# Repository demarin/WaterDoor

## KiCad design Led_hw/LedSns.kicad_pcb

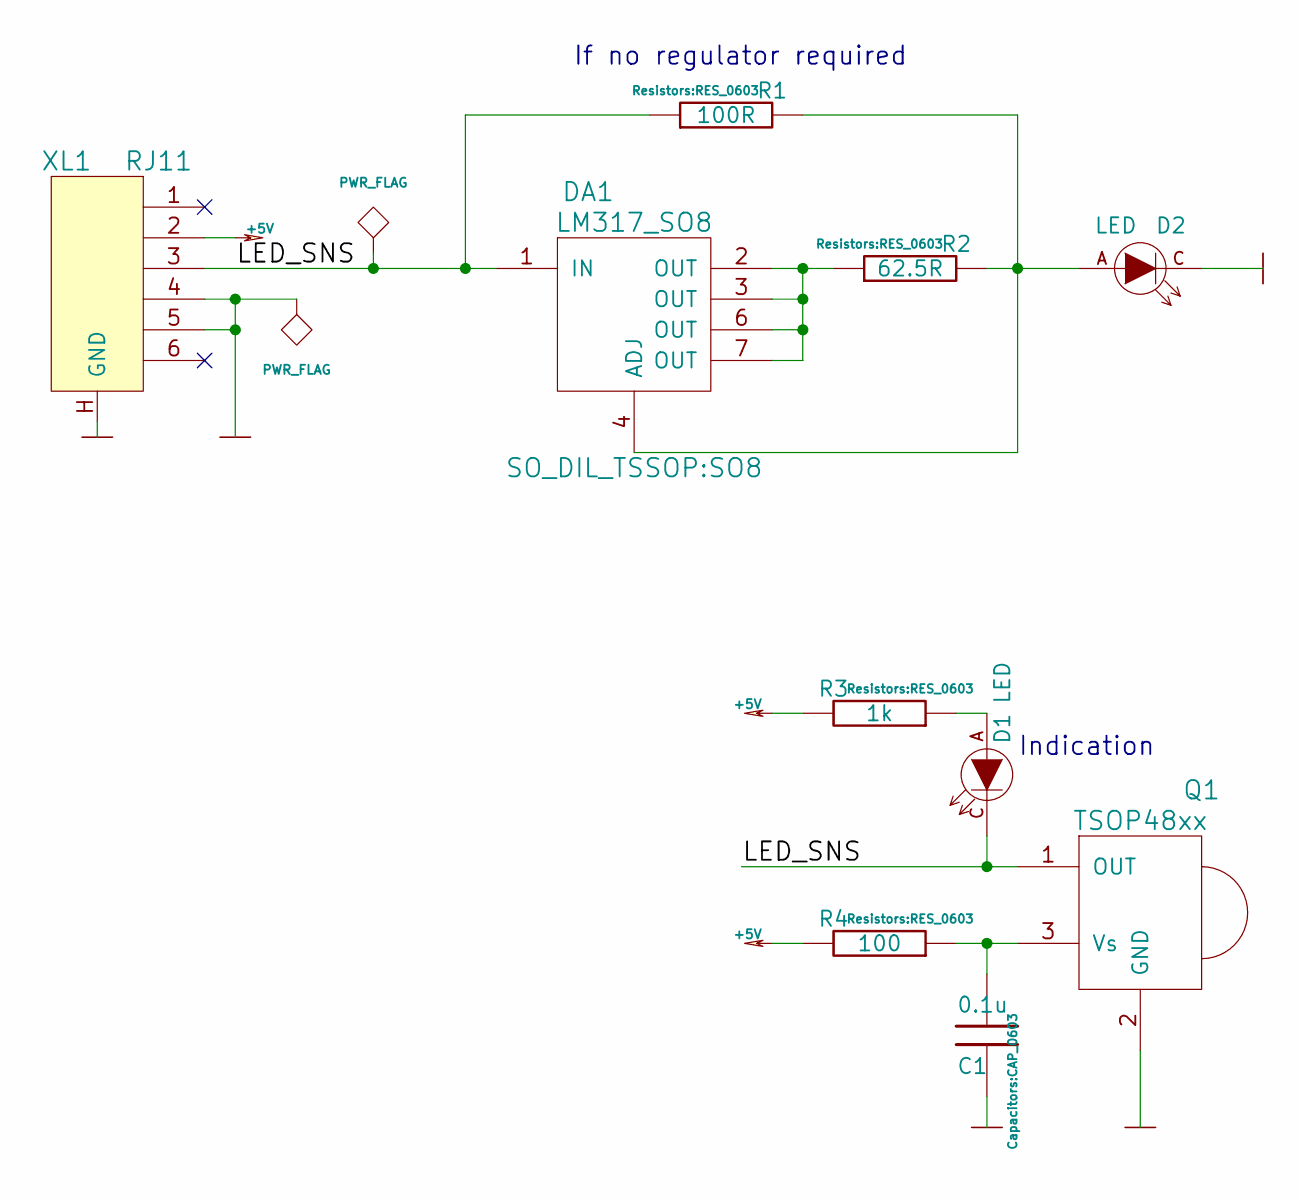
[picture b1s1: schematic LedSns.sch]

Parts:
C1: 0.1u; CAP_0603
D1: LED; Through-Hole-3mm
D2: LED; Through-Hole-5mm
DA1: LM317_SO8; SO8
Q1: TSOP48xx
R1: 100R; RES_0603
R2: 62.5R; RES_0603
R3: 1k; RES_0603
R4: 100; RES_0603
XL1: RJ11; RJ11_TJ6_6P6C

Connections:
+5V: R3.2, R4.2, XL1.2
/LED_SNS: D1.C, DA1.1 (IN), Q1.1 (OUT), R1.1, XL1.3
GND: C1.2, D2.C, Q1.2 (GND), XL1.4, XL1.5, XL1.H (GND)
unnamed: C1.1, Q1.3 (Vs), R4.1
unnamed: D1.A, R3.1
unnamed: D2.A, DA1.4 (ADJ), R1.2, R2.2
unnamed: DA1.2 (OUT), DA1.3 (OUT), DA1.6 (OUT), DA1.7 (OUT), R2.1

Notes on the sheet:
If no regulator required
Indication

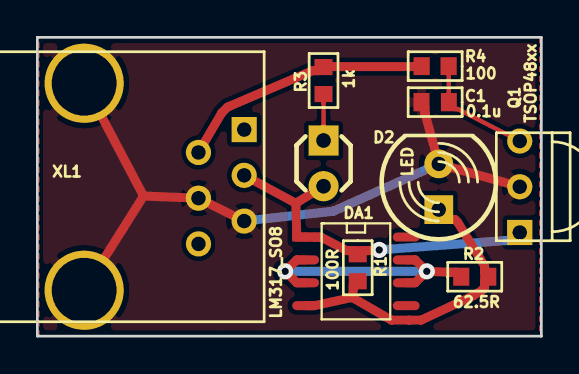
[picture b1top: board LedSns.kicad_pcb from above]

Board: 2 copper layers, 28.0 x 16.6 mm, 10 parts (0 on the bottom side), 7 nets.

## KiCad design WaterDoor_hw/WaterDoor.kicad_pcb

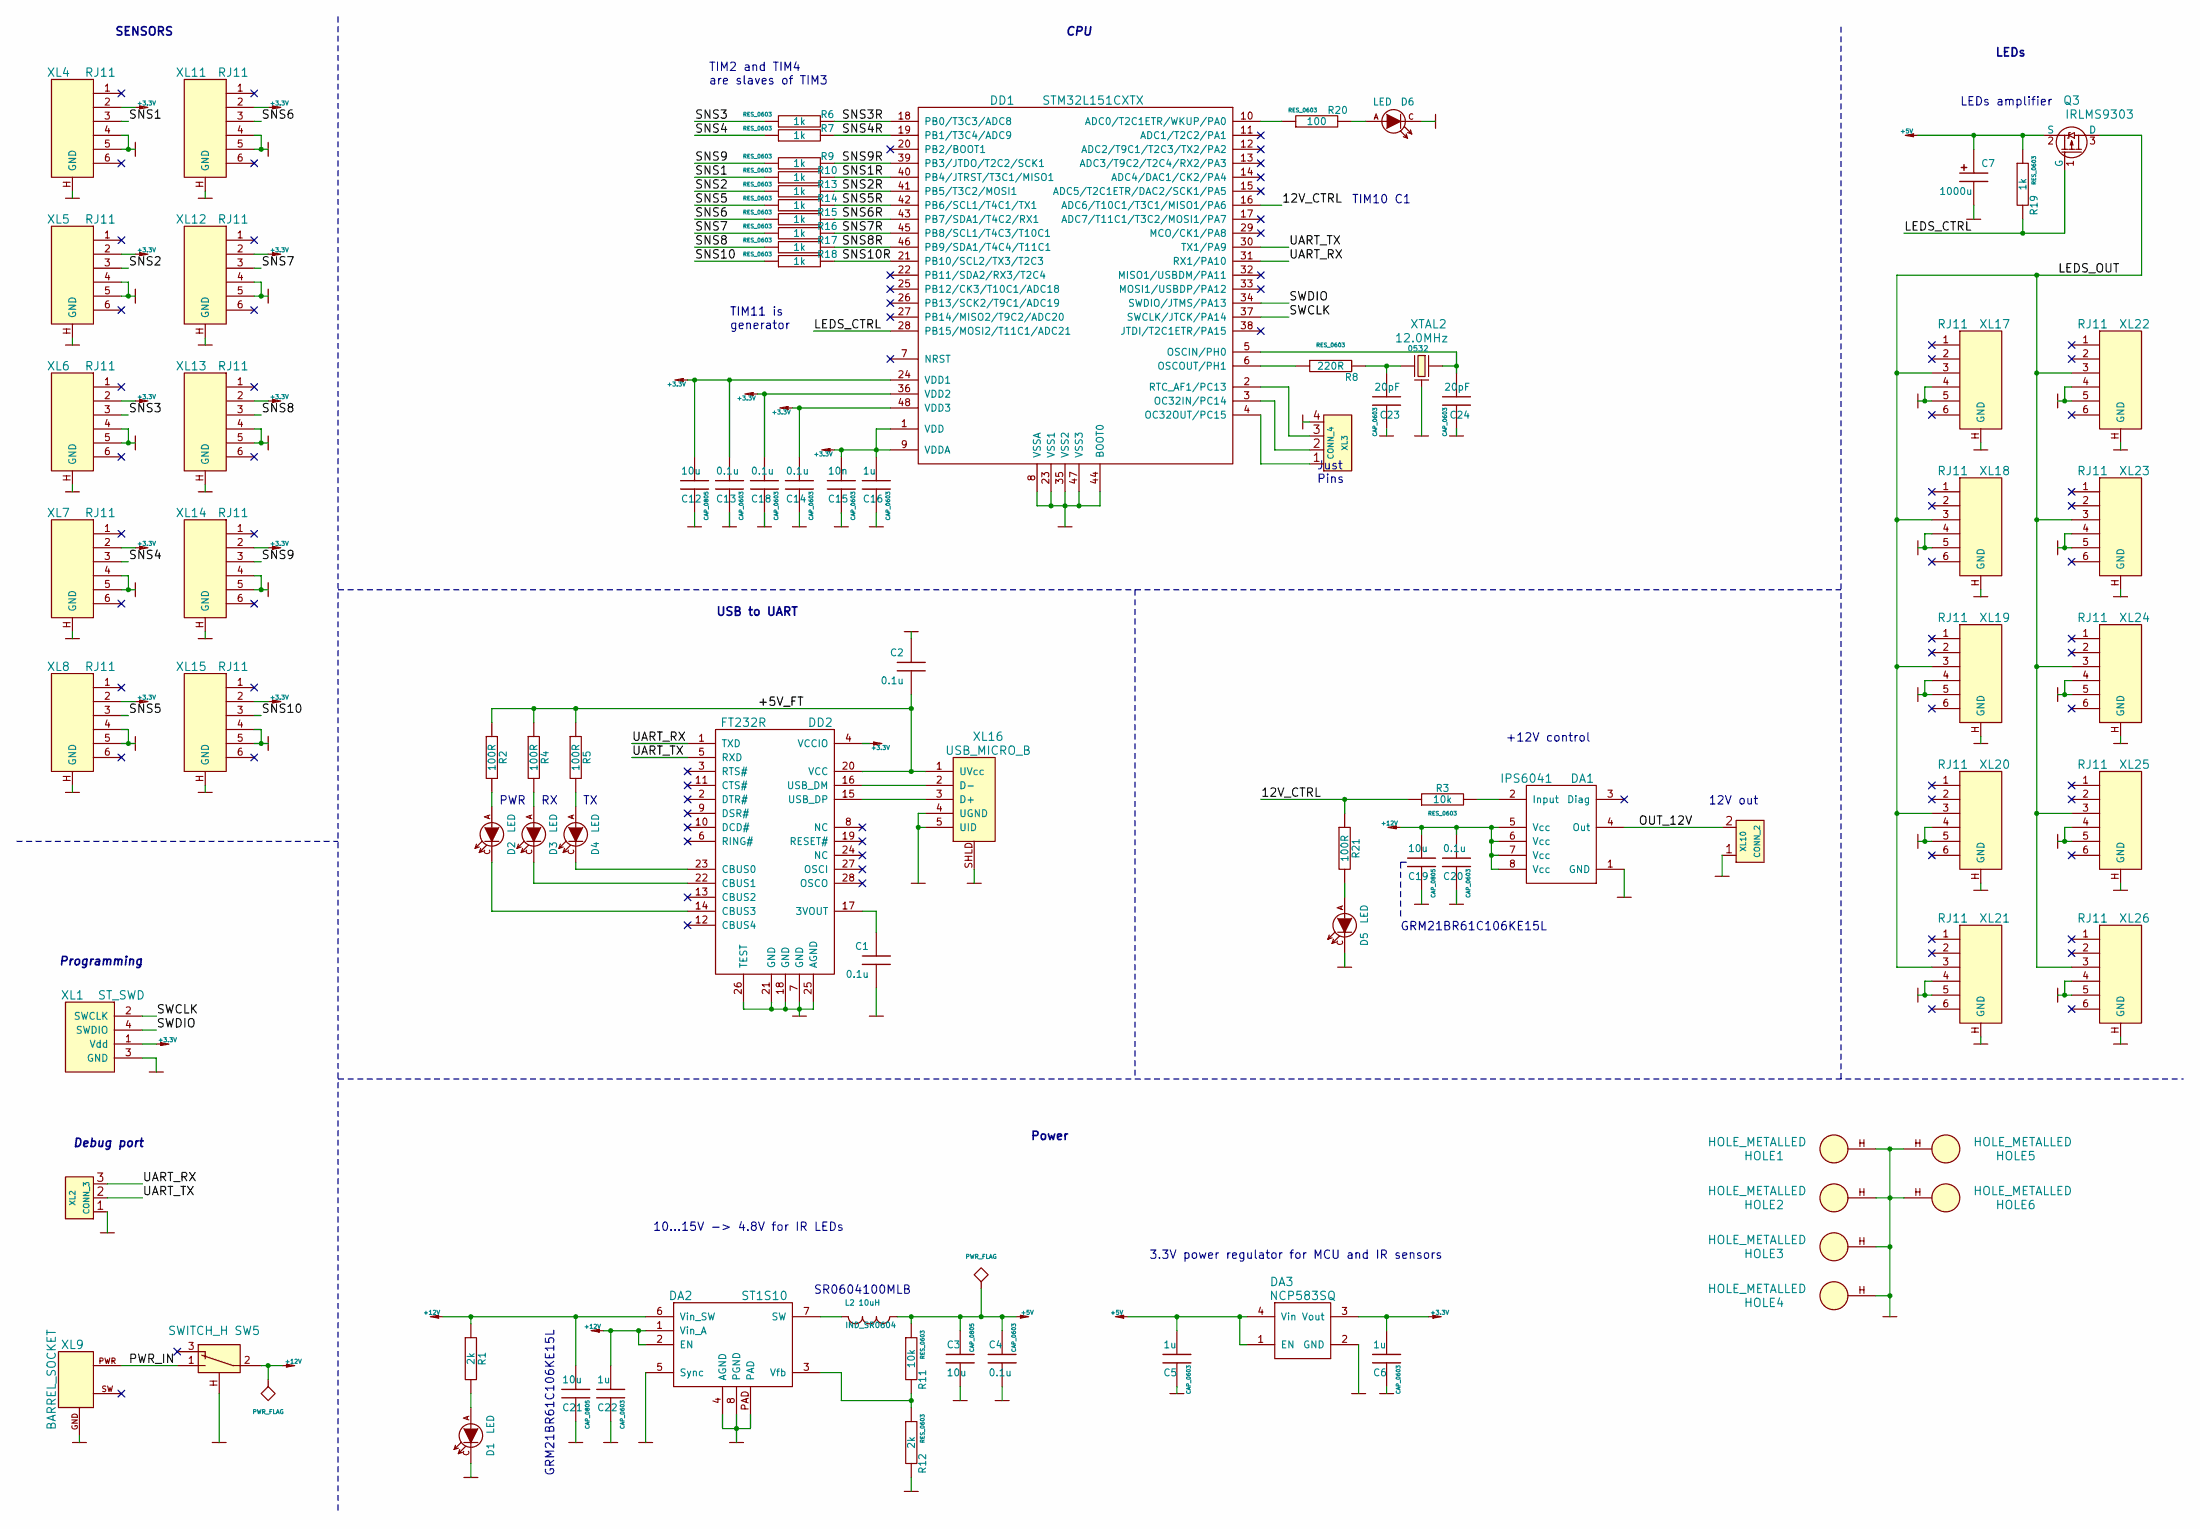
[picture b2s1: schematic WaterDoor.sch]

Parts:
C1, C2: 0.1u
C3, C12, C19, C21: 10u; CAP_0805
C4, C13, C14, C18, C20: 0.1u; CAP_0603
C5, C6, C16, C22: 1u; CAP_0603
C7: 1000u
C15: 10n; CAP_0603
C23, C24: 20pF; CAP_0603
D1, D2, D3, D4, D5, D6: LED
DA1: IPS6041
DA2: ST1S10
DA3: NCP583SQ
DD1: STM32L151CXTX
DD2: FT232R
HOLE1, HOLE2, HOLE3, HOLE4, HOLE5, HOLE6: HOLE_METALLED
L2: 10uH; IND_SR0604
Q3: IRLMS9303
R1: 2k
R2, R4, R5, R21: 100R
R3, R11: 10k; RES_0603
R6, R7, R9, R10, R13, R14, R15, R16, R17, R18, R19: 1k; RES_0603
R8: 220R; RES_0603
R12: 2k; RES_0603
R20: 100; RES_0603
SW5: SWITCH_H
XL1: ST_SWD
XL2: CONN_3
XL3: CONN_4
XL4, XL5, XL6, XL7, XL8, XL11, XL12, XL13, XL14, XL15, XL17, XL18, XL19, XL20, XL21, XL22, XL23, XL24, XL25, XL26: RJ11
XL9: BARREL_SOCKET
XL10: CONN_2
XL16: USB_MICRO_B
XTAL2: 12.0MHz; 0532

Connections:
+3.3V: C6.1, C12.1, C13.1, C14.1, C15.1, C16.1, C18.1, DA3.3 (Vout), DD1.1 (VDD), DD1.9 (VDDA), DD1.24 (VDD1), DD1.36 (VDD2), DD1.48 (VDD3), DD2.4 (VCCIO), XL1.1 (Vdd), XL4.2, XL5.2, XL6.2, XL7.2, XL8.2, XL11.2, XL12.2, XL13.2, XL14.2, XL15.2
+5V: C3.2, C4.2, C5.1, C7.1, DA3.1 (EN), DA3.4 (Vin), L2.1, Q3.2 (S), R11.1, R19.1
+12V: C19.1, C20.1, C21.1, C22.1, DA1.5 (Vcc), DA1.6 (Vcc), DA1.7 (Vcc), DA1.8 (Vcc), DA2.1 (Vin_A), DA2.2 (EN), DA2.6 (Vin_SW), R1.1, SW5.2
/12V_CTRL: DD1.16 (ADC6/T10C1/T3C1/MISO1/PA6), R3.1, R21.1
/+5V_FT: C2.2, DD2.20 (VCC), R2.1, R4.1, R5.1, XL16.1 (UVcc)
/LEDS_CTRL: DD1.28 (PB15/MOSI2/T11C1/ADC21), Q3.1 (G), R19.2
/LEDS_OUT: Q3.3 (D), XL17.3, XL18.3, XL19.3, XL20.3, XL21.3, XL22.3, XL23.3, XL24.3, XL25.3, XL26.3
/OUT_12V: DA1.4 (Out), XL10.2 (PM)
/PWR_IN: SW5.1, XL9.PWR
/SNS1: R10.1, XL4.3
/SNS1R: DD1.40 (PB4/JTRST/T3C1/MISO1), R10.2
/SNS2: R13.1, XL5.3
/SNS2R: DD1.41 (PB5/T3C2/MOSI1), R13.2
/SNS3: R6.1, XL6.3
/SNS3R: DD1.18 (PB0/T3C3/ADC8), R6.2
/SNS4: R7.1, XL7.3
/SNS4R: DD1.19 (PB1/T3C4/ADC9), R7.2
/SNS5: R14.1, XL8.3
/SNS5R: DD1.42 (PB6/SCL1/T4C1/TX1), R14.2
/SNS6: R15.1, XL11.3
/SNS6R: DD1.43 (PB7/SDA1/T4C2/RX1), R15.2
/SNS7: R16.1, XL12.3
/SNS7R: DD1.45 (PB8/SCL1/T4C3/T10C1), R16.2
/SNS8: R17.1, XL13.3
/SNS8R: DD1.46 (PB9/SDA1/T4C4/T11C1), R17.2
/SNS9: R9.1, XL14.3
/SNS9R: DD1.39 (PB3/JTDO/T2C2/SCK1), R9.2
/SNS10: R18.1, XL15.3
/SNS10R: DD1.21 (PB10/SCL2/TX3/T2C3), R18.2
/SWCLK: DD1.37 (SWCLK/JTCK/PA14), XL1.2 (SWCLK)
/SWDIO: DD1.34 (SWDIO/JTMS/PA13), XL1.4 (SWDIO)
/UART_RX: DD1.31 (RX1/PA10), DD2.1 (TXD), XL2.3
/UART_TX: DD1.30 (TX1/PA9), DD2.5 (RXD), XL2.2 (PM)
GND: C1.2, C2.1, C3.1, C4.1, C5.2, C6.2, C7.2, C12.2, C13.2, C14.2, C15.2, C16.2, C18.2, C19.2, C20.2, C21.2, C22.2, C23.2, C24.2, D1.C, D5.C, D6.C, DA1.1 (GND), DA2.4 (AGND), DA2.5 (Sync), DA2.8 (PGND), DA2.PAD, DA3.2 (GND), DD1.8 (VSSA), DD1.23 (VSS1), DD1.35 (VSS2), DD1.44 (BOOT0), DD1.47 (VSS3), DD2.7 (GND), DD2.18 (GND), DD2.21 (GND), DD2.25 (AGND), DD2.26 (TEST), HOLE1.H, HOLE2.H, HOLE3.H, HOLE4.H, HOLE5.H, HOLE6.H, R12.2, SW5.H, XL1.3 (GND), XL2.1, XL3.4, XL4.4, XL4.5, XL4.H (GND), XL5.4, XL5.5, XL5.H (GND), XL6.4, XL6.5, XL6.H (GND), XL7.4, XL7.5, XL7.H (GND), XL8.4, XL8.5, XL8.H (GND), XL9.GND, XL10.1, XL11.4, XL11.5, XL11.H (GND), XL12.4, XL12.5, XL12.H (GND), XL13.4, XL13.5, XL13.H (GND), XL14.4, XL14.5, XL14.H (GND), XL15.4, XL15.5, XL15.H (GND), XL16.4 (UGND), XL16.5 (UID), XL16.SHLD, XL17.4, XL17.5, XL17.H (GND), XL18.4, XL18.5, XL18.H (GND), XL19.4, XL19.5, XL19.H (GND), XL20.4, XL20.5, XL20.H (GND), XL21.4, XL21.5, XL21.H (GND), XL22.4, XL22.5, XL22.H (GND), XL23.4, XL23.5, XL23.H (GND), XL24.4, XL24.5, XL24.H (GND), XL25.4, XL25.5, XL25.H (GND), XL26.4, XL26.5, XL26.H (GND), XTAL2.H
unnamed: C1.1, DD2.17 (3VOUT)
unnamed: C23.1, R8.2, XTAL2.2
unnamed: C24.1, DD1.5 (OSCIN/PH0), XTAL2.1
unnamed: D1.A, R1.2
unnamed: D2.A, R2.2
unnamed: D2.C, DD2.14 (CBUS3)
unnamed: D3.A, R4.2
unnamed: D3.C, DD2.22 (CBUS1)
unnamed: D4.A, R5.2
unnamed: D4.C, DD2.23 (CBUS0)
unnamed: D5.A, R21.2
unnamed: D6.A, R20.2
unnamed: DA1.2 (Input), R3.2
unnamed: DA2.3 (Vfb), R11.2, R12.1
unnamed: DA2.7 (SW), L2.2
unnamed: DD1.2 (RTC_AF1/PC13), XL3.3
unnamed: DD1.3 (OC32IN/PC14), XL3.2 (PM)
unnamed: DD1.4 (OC32OUT/PC15), XL3.1
unnamed: DD1.6 (OSCOUT/PH1), R8.1
unnamed: DD1.10 (ADC0/T2C1ETR/WKUP/PA0), R20.1
unnamed: DD2.15 (USB_DP), XL16.3 (D+)
unnamed: DD2.16 (USB_DM), XL16.2 (D-)

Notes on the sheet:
Debug port
Programming
CPU
Power
Just Pins
GRM21BR61C106KE15L
SR0604100MLB
10...15V -> 4.8V for IR LEDs
12V out
LEDs amplifier
+12V control
LEDs
TIM2 and TIM4 are slaves of TIM3
SENSORS
TIM11 is generator
PWR
TIM10 C1
USB to UART
3.3V power regulator for MCU and IR sensors

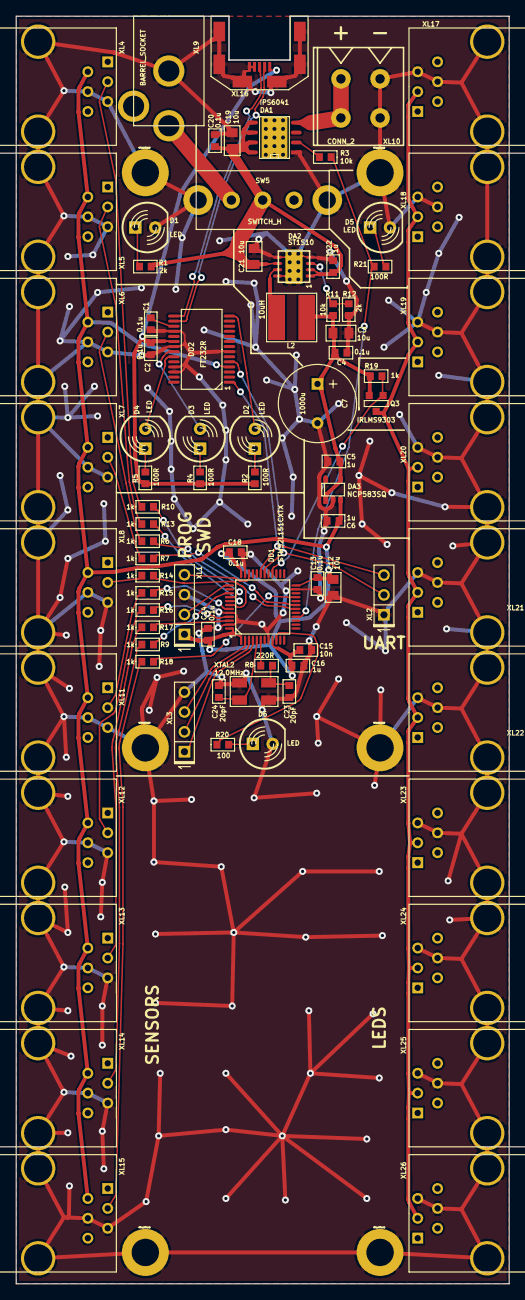
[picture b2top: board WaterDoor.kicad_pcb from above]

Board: 2 copper layers, 63.0 x 162.0 mm, 87 parts (0 on the bottom side), 56 nets.

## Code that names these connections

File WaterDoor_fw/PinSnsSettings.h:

/*
 * SnsPins.h
 *
 *  Created on: 17 ÿíâ. 2015 ã.
 *      Author: Kreyl
 */

/* ================ Documentation =================
 * There are several (may be 1) groups of sensors (say, buttons and USB connection).
 * There is GPIO and Pin data for every sensor.
 *
 */

#ifndef PINSNSSETTINGS_H_
#define PINSNSSETTINGS_H_

#define SIMPLESENSORS_ENABLED   TRUE

#if SIMPLESENSORS_ENABLED
#include "ch.h"
#include "hal.h"
#ifdef STM32F2XX
#include "kl_lib_f2xx.h"
#elif defined STM32L1XX_MD || defined STM32L1XX_HD
#include "kl_lib_L15x.h"
#endif

#include "main.h" // App.thd here
#include "evt_mask.h"

#define SNS_POLL_PERIOD_MS  1

enum PinSnsState_t {pssLo, pssHi, pssRising, pssFalling};
typedef void (*ftVoidPSnsStLen)(PinSnsState_t *PState, uint32_t Len);

// Single pin setup data
struct PinSns_t {
    GPIO_TypeDef *PGpio;
    uint16_t Pin;
    PinPullUpDown_t Pud;
    ftVoidPSnsStLen Postprocessor;
    void Init() const { PinSetupIn(PGpio, Pin, Pud); }
    void Off()  const { PinSetupAnalog(PGpio, Pin);  }
    bool IsHi() const { return PinIsSet(PGpio, Pin); }
};

// ================================= Settings ==================================
// Motion sensors handler
void ProcessSensors(PinSnsState_t *PState, uint32_t Len);
void ProcessLastSensor(PinSnsState_t *PState, uint32_t Len);
void ProcessExitSensor(PinSnsState_t *PState, uint32_t Len);

const PinSns_t PinSns[] = {
        {GPIOB,  4, pudPullUp, ProcessSensors}, // SNS1
        {GPIOB,  5, pudPullUp, ProcessSensors}, // SNS2
        {GPIOB,  0, pudPullUp, ProcessSensors}, // SNS3
        {GPIOB,  1, pudPullUp, ProcessSensors}, // SNS4
        {GPIOB,  6, pudPullUp, ProcessSensors}, // SNS5
        {GPIOB,  7, pudPullUp, ProcessSensors}, // SNS6
        {GPIOB,  8, pudPullUp, ProcessLastSensor}, // SNS7
        {GPIOB,  9, pudPullUp, ProcessLastSensor}, // SNS8
        {GPIOB,  3, pudPullUp, ProcessExitSensor}, // SNS9
        {GPIOB, 10, pudPullUp, ProcessExitSensor}, // SNS10
};
#define PIN_SNS_CNT     countof(PinSns)

#endif

#endif /* PINSNSSETTINGS_H_ */

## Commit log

2015-04-23 Sch seems nearly ready
2015-04-25 + Main PCB ready for production
2015-04-25 + LedSNS completed PCBs sent to production
2015-04-28 + Firmware development started
2015-05-01 + IR LED generating - PwmPin
2015-05-01 + Output12V
2015-05-01 Sensor metering seems completed
2015-05-02 + Led repeated blink
2015-05-04 basic functionality added
2015-05-12 Now it really works
2015-05-14 closing issue #6
2015-05-15 Closing issue #5. Using existing LED.
2015-05-21 Final parameters set Fixed possible bug with double overflow on large time values Fixed bug with multiple linreg call
